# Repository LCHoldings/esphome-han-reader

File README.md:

[![Contributors][contributors-shield]][contributors-url] [![Forks][forks-shield]][forks-url] [![Stargazers][stars-shield]][stars-url] [![Issues][issues-shield]][issues-url]

<!-- PROJECT LOGO -->
<br />
<div align="center">

  <h3 align="center">ESP Home HAN Reader</h3>
  <p align="center">
    Get your power usage in realtime with extreme detail using the HAN-port.
    <br />
    <a href="https://github.com/hackclub/OnBoard/pull/1363">OnBoard PR</a>
    ·
    <a href="https://github.com/LCHoldings/esphome-han-reader/issues/new?labels=bug&template=bug-report---.md">Report Bug</a>
    ·
    <a href="https://github.com/LCHoldings/esphome-han-reader/fork">Fork Project</a>
  </p>
</div>

<!-- ABOUT THE PROJECT -->
## 📝 About The Project

In Sweden and Norway afaik we have a port on our electrical meters called the [HAN-port](https://github.com/u9n/hanporten) (Home Area Network), with this port you can get details about your power usage in almost realtime and with extreme detail compared to alternatives. I use Home Assistant in my home and we recently got our electrical meter replaced with one that has a HAN-port so I saw that as an perfect opportunity to learn some stuff and have fun.

<p align="right">(<a href="#readme-top">back to top</a>)</p>

### 🛠️ Made using

This section contains some of the most notable tools/libraries used in this project.

* [![KiCad](https://img.shields.io/badge/kicad-000000?style=for-the-badge&logo=kicad&color=314CB0
)](https://slack.com)
* [![ESPHome](https://img.shields.io/badge/esphome-000000?style=for-the-badge&logo=esphome&color=000000
)](https://esphome.io)

<p align="right">(<a href="#readme-top">back to top</a>)</p>

<!-- ROADMAP -->
## 🗺️ Roadmap

- [X] 🚢 Release project
- [X] 🖌️ Make ground fill
- [ ] 🤏 More compact design
- [ ] 📦 3D Printable Case
- [ ] 📡 Mouting for external antenna

<p align="right">(<a href="#readme-top">back to top</a>)</p>

<!-- CONTRIBUTING -->
## ⛑️ Contributing

Contributions are what make the open source community such an amazing place to learn, inspire, and create. Any contributions you make are **greatly appreciated**.

If you have a suggestion that would make the portfolio better, please fork the repo and create a pull request. You can also simply open an issue with the tag "enhancement".
Don't forget to give the project a star! Thanks!

1. Fork the Project
2. Change the project and add your files or changes (`git add *`)
3. Commit your Changes (`git commit -m 'Feat | Added XXXX to the XXX'`)
4. Push to the Branch (`git push`)
5. Open a Pull Request

### 🏆 Top contributors:

<p align="right">(<a href="#readme-top">back to top</a>)</p>

<!-- CONTACT -->
## 💌 Contact

Lazyllama - [@Lazyllamaa](https://discord.com/users/754965470888722484) - me@lazyllama.xyz

Project Link: [https://github.com/lcholdings/esphome-han-reader](https://github.com/lcholdings/esphome-han-reader)

<p align="right">(<a href="#readme-top">back to top</a>)</p>

<!-- ACKNOWLEDGMENTS -->
## 🌟 Acknowledgments

Thanks to the following people for their help and inspiration:

* [Readme Template](https://github.com/othneildrew/Best-README-Template)
* [OnBoard](https://hackclub.com/onboard/)
* [Cyber](https://github.com/cyberdev-tech)
* [Hack Club](https://hackclub.com)
* [ESP Home P1 Reader](https://github.com/psvanstrom/esphome-p1reader)
<p align="right">(<a href="#readme-top">back to top</a>)</p>

<!-- MARKDOWN LINKS & IMAGES -->
<!-- https://www.markdownguide.org/basic-syntax/#reference-style-links -->
[contributors-shield]: https://img.shields.io/github/contributors/lcholdings/esphome-han-reader.svg?style=for-the-badge
[contributors-url]: https://github.com/lcholdings/esphome-han-reader/graphs/contributors
[forks-shield]: https://img.shields.io/github/forks/lcholdings/esphome-han-reader.svg?style=for-the-badge
[forks-url]: https://github.com/lcholdings/esphome-han-reader/network/members
[stars-shield]: https://img.shields.io/github/stars/lcholdings/esphome-han-reader.svg?style=for-the-badge
[stars-url]: https://github.com/lcholdings/esphome-han-reader/stargazers
[issues-shield]: https://img.shields.io/github/issues/lcholdings/esphome-han-reader.svg?style=for-the-badge
[issues-url]: https://github.com/lcholdings/esphome-han-reader/issues

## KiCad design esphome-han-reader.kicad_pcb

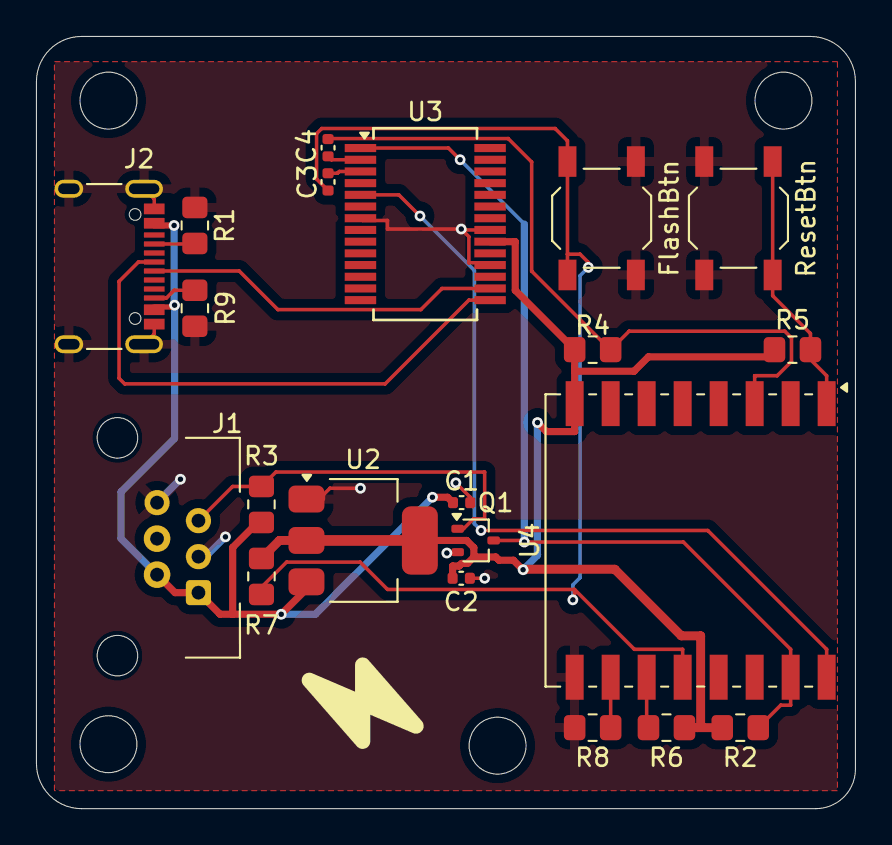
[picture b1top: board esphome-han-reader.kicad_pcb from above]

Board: 2 copper layers, 45.5 x 42.9 mm, 21 parts (0 on the bottom side), 17 nets.

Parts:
C1, C2: 22uF; C_0402_1005Metric
C3, C4: 0.1 µF; C_0402_1005Metric
J1: RJ12; RJ12_DS1133-S60BPX
J2: YTC-TC16-473; USB_C_Receptacle_XKB_U262-16XN-4BVC11
Q1: BC817W; SOT-323_SC-70
R1, R9: 5K1; R_0805_2012Metric_Pad1.20x1.40mm_HandSolder
R2, R4, R5, R6, R7, R8: 10K; R_0805_2012Metric_Pad1.20x1.40mm_HandSolder
R3: 4K7; R_0805_2012Metric_Pad1.20x1.40mm_HandSolder
SW1: ResetBtn; SW_SPST_TL3342
SW2: FlashBtn; SW_SPST_TL3342
U2: TLV1117LV33DCYT; SOT-223-3_TabPin2
U3: FT232RL; SSOP-28_5.3x10.2mm_P0.65mm
U4: ESP-07

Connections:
+3V3: C2.1, R2.2, R4.1, R5.1, R6.1, R7.1, U2.2 (VO), U3.20 (VCC), U4.8 (VCC)
+5V: C1.2, J1.1, J1.2, J2.A4 (VBUS), J2.A9 (VBUS), J2.B4 (VBUS), J2.B9 (VBUS), R3.1, U2.3 (VI)
EN: C4.1, R4.2, U4.3 (EN)
ESP-RX: Q1.3 (C), R2.1, U3.1 (TXD), U4.15 (GPIO3/RXD)
ESP-TX: U3.5 (RXD), U4.16 (GPIO1/TXD)
FTDI-DTR: C4.2, U3.2 (DTR)
FTDI-RTS: C3.2, U3.3 (RTS)
GND: C1.1, C2.2, J1.3, J1.6, J2.A1 (GND), J2.A12 (GND), J2.B1 (GND), J2.B12 (GND), J2.S1 (SHIELD), Q1.2 (E), R1.1, R8.2, R9.1, SW1.1, SW2.2, U2.1 (GND), U3.7 (GND), U3.18 (GND), U3.21 (GND), U4.9 (GND)
GPIO 0: C3.1, R7.2, SW2.1, U4.12 (GPIO0)
GPIO 2: R6.2, U4.11 (GPIO2)
unnamed: J1.5, Q1.1 (B), R3.2
unnamed: R8.1, U4.10 (GPIO15)
RESET: R5.2, SW1.2, U4.1 (~RST)
USB-CC1: J2.A5 (CC1), R1.2
USB-CC2: J2.B5 (CC2), R9.2
USB-DNEG: J2.A7 (D-), U3.16 (USBD-)
USB-DPOS: J2.A6 (D+), U3.15 (USBD+)

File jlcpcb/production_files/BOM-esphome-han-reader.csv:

Comment,Designator,Footprint,LCSC,Quantity
0.1 µF,"C3,C4",C_0402_1005Metric,C1525,2
10K,"R2,R4,R5,R6,R7,R8",R_0805_2012Metric_Pad1.20x1.40mm_HandSolder,C17414,6
4K7,R3,R_0805_2012Metric_Pad1.20x1.40mm_HandSolder,C17673,1
5K1,"R1,R9",R_0805_2012Metric_Pad1.20x1.40mm_HandSolder,C23186,2
TLV1117LV33DCYT,U2,SOT-223-3_TabPin2,C2877977,1
ResetBtn,"SW1,SW2",SW_SPST_TL3342,C318884,2
YTC-TC16-473,J2,USB_C_Receptacle_XKB_U262-16XN-4BVC11,C5329561,1
22uF,"C1,C2",C_0402_1005Metric,C5672,2
BC817W,Q1,SOT-323_SC-70,C75566,1
RJ12,J1,RJ12_DS1133-S60BPX,C77859,1
ESP-07,U4,ESP-07,C82894,1
FT232RL,U3,SSOP-28_5.3x10.2mm_P0.65mm,C8690,1

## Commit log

2024-12-19 feat: I'm cooking 🔥
    TODO: add interferance remover switch and make 3d model case.
2024-12-21 feat: Final Rev??
2024-12-21 fix: make high seas readme render correctly 🧰
2024-12-21 feat: Gerber file 📁
2024-12-23 feat: new design, new caps and onboard programmer.
2024-12-24 feat: actually final revision. PR merged and PCBs ordered.
2024-12-24 feat: Greenscreen IMG
2024-12-24 feat: PCB Image
2024-12-24 feat: highseas image 🚢
